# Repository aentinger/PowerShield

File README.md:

💾 Power Shield
===============

# 📸 Image

# 📂 Description

The LXRobotics Power Shield facilitates the high power supply of an Arduino Board over a wide input voltage range. Furthermore, the Power Shield allows the usage of Shields with high power requirements, which can not be supplied solely by the linear regulator of the Arduino (such as the Servo Shield when connecting 18 servos). A reverse polarity protection protects the Power Shield against destruction caused by faulty connections of the input voltage.

**Features**

* High power supply over wide input voltage rande 6 - 24 V DC
* Allows usage of Shields with high power requirements ()
* Reverse polarity protection
* Status-LED
* High-quality pluggable screw terminals for easy and stable connection of the supply

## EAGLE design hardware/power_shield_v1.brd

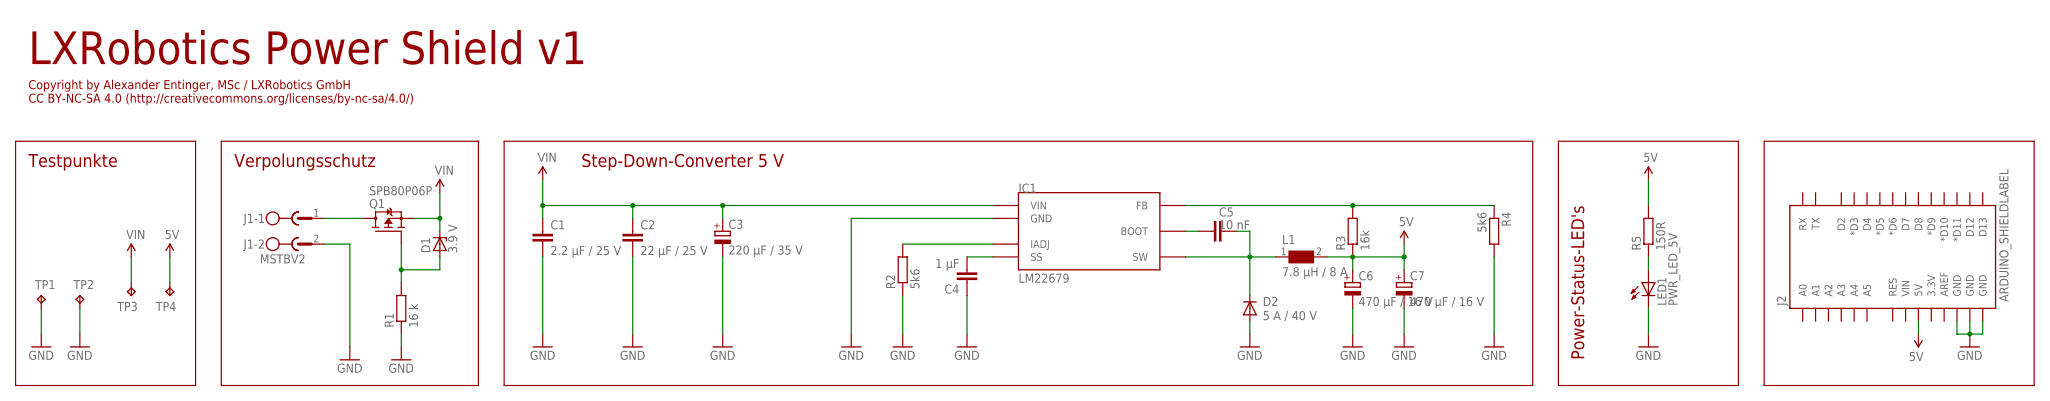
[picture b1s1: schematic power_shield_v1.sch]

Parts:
C1: 2.2 µF / 25 V; C1206
C2: 22 µF / 25 V; C1210
C3: 220 µF / 35 V; PANASONIC_F
C4: 1 µF; C0805
C5: 10 nF; C0805
C6, C7: 470 µF / 16 V; PANASONIC_F
D1: 3.9 V; SMB
D2: 5 A / 40 V; SMC
IC1: LM22679; P-TO263-7-1
J1: MSTBV2
J2: ARDUINO_SHIELDLABEL; DUEMILANOVE_SHIELD
L1: 7.8 µH / 8 A; WE-HCI_1050
LED1: PWR_LED_5V; CHIPLED_0805
Q1: SPB80P06P; TO263
R1: 16 k; M0805
R2, R4: 5k6; M0805
R3: 16k; M0805
R5: 150R; M0805
TP1, TP2, TP3, TP4: TPB1,27; B1,27

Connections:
5V: C6.+, C7.+, J2.5V, L1.2, R3.1, R5.2, TP4.TP
GND: C1.2, C2.2, C3.-, C4.1, C6.-, C7.-, D2.A, IC1.4 (GND), IC1.TH (GND), J1.2, J2.GND@0 (GND), J2.GND@1 (GND), J2.GND@2 (GND), LED1.C, R1.1, R2.1, R4.2, TP1.TP, TP2.TP
unnamed: IC1.5 (IADJ), R2.2
unnamed: C4.2, IC1.7 (SS)
unnamed: IC1.6 (FB), R3.2, R4.1
unnamed: C5.1, IC1.3 (BOOT)
unnamed: C5.2, D2.C, IC1.1 (SW), L1.1
unnamed: LED1.A, R5.1
unnamed: D1.A, Q1.1 (G), R1.2
unnamed: J1.1, Q1.3 (D)
VIN: C1.1, C2.1, C3.+, D1.C, IC1.2 (VIN), Q1.2 (S), TP3.TP

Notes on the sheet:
Verpolungsschutz
Testpunkte
LXRobotics Power Shield v1
Step-Down-Converter 5 V
Power-Status-LED's
Copyright by Alexander Entinger, MSc / LXRobotics GmbH CC BY-NC-SA 4.0 (http://creativecommons.org/licenses/by-nc-sa/4.0/)

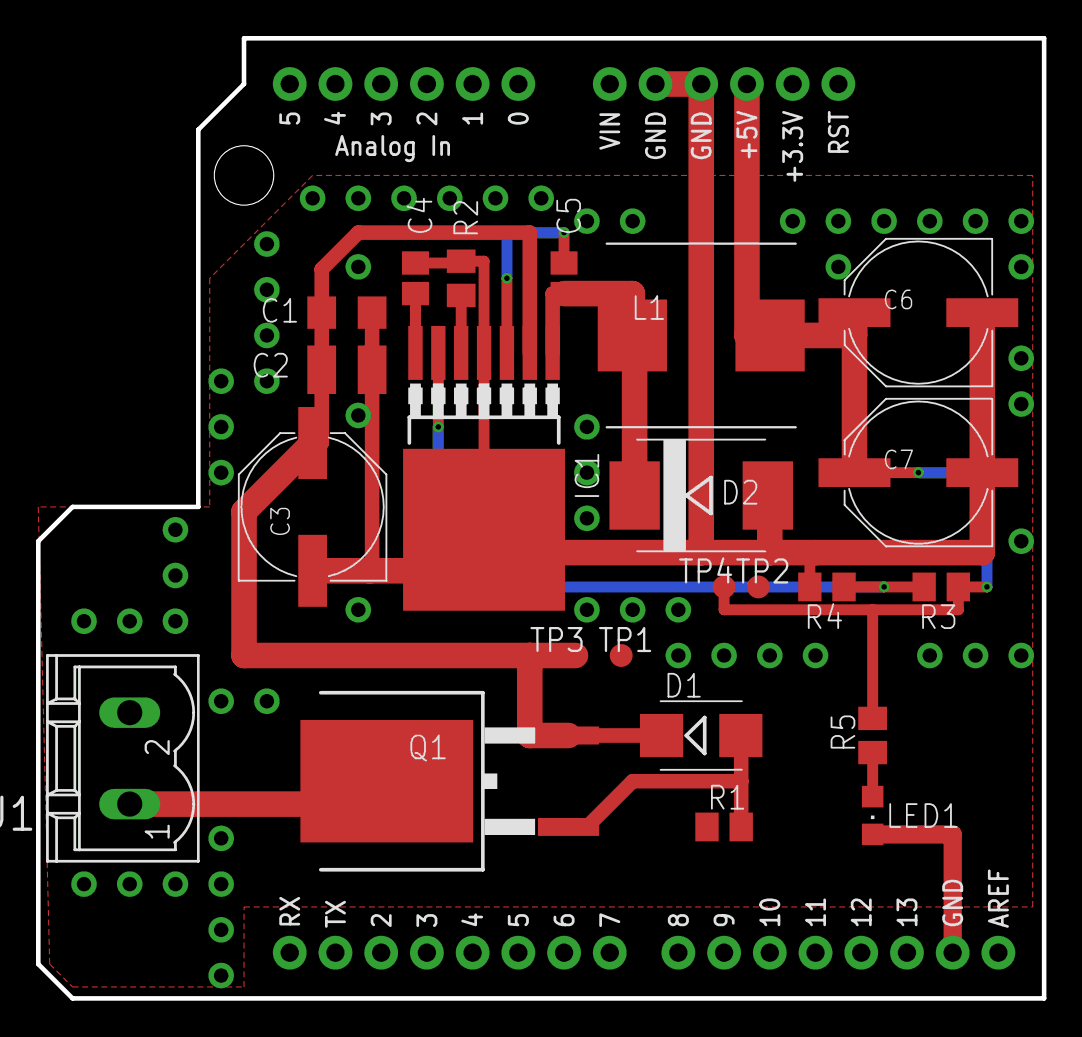
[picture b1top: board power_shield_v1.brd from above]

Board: 2 copper layers, 55.9 x 53.3 mm, 24 parts (0 on the bottom side), 11 nets.

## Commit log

2015-04-20 adding readme and schematic
2017-06-27 Adding hardware + images
2025-03-26 Pretty up README.
2025-03-26 Uploading BOM.
2025-03-26 Use relative link.

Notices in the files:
README.md:
License: CC BY-NC-SA 4.0
parts and their libraries:
SparkFun-Boards: Licensing: CC v3.0 Share-Alike You are welcome to use this library for commercial purposes.
